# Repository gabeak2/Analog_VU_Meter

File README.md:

# Analog_VU_Meter

My First PCB - a VU-Meter with a microphone, and 2 LM3915 Bar Graph Displays.  It worked okay, there was always an issue with the crossover voltage of the LM3915s.  Reboots I did used MCUs, with much better results.

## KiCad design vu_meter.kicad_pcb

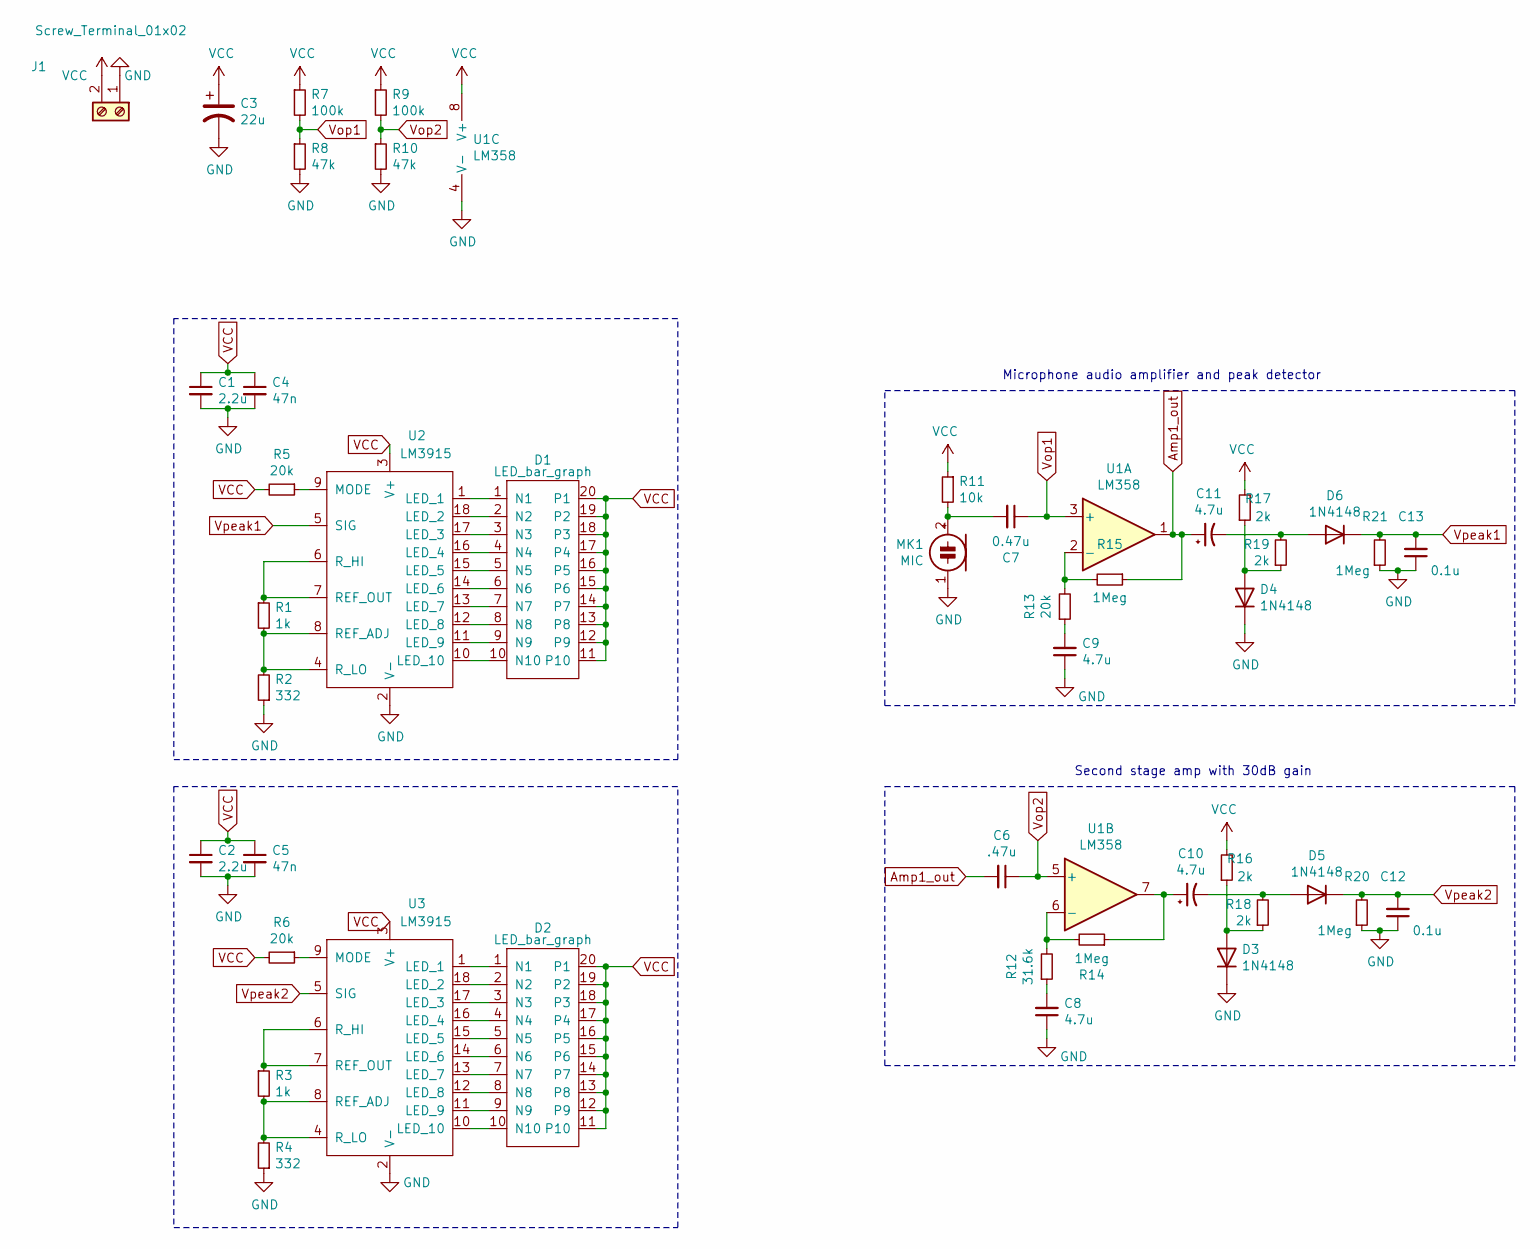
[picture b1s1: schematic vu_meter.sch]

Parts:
C1, C2: 2.2u; C_0805_2012Metric
C3: 22u; C_0805_2012Metric
C4, C5: 47n; C_0805_2012Metric
C6: .47u; C_0805_2012Metric
C7: 0.47u; C_0805_2012Metric
C8, C9, C10, C11: 4.7u; C_0805_2012Metric
C12, C13: 0.1u; C_0805_2012Metric
D1, D2: LED_bar_graph
D3, D4, D5, D6: 1N4148; D_DO-35_SOD27_P7.62mm_Horizontal
J1: Screw_Terminal_01x02; screw_terminal
MK1: MIC; screw_terminal
R1, R3: 1k; R_0805_2012Metric
R2, R4: 332; R_0805_2012Metric
R5, R6, R13: 20k; R_0805_2012Metric
R7, R9: 100k; R_0805_2012Metric
R8, R10: 47k; R_0805_2012Metric
R11: 10k; R_0805_2012Metric
R12: 31.6k; R_0805_2012Metric
R14, R15, R20, R21: 1Meg; R_0805_2012Metric
R16, R17, R18, R19: 2k; R_0805_2012Metric
U1: LM358; lm358
U2, U3: LM3915; LM3915_PDIP

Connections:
Amp1_out: C6.2, C11.1, R15.1, U1.1
GND: C1.2, C2.2, C3.2, C4.2, C5.2, C8.1, C9.1, C12.1, C13.1, D3.1 (K), D4.1 (K), J1.1, MK1.1 (-), R2.1, R4.1, R8.2, R10.2, R20.1, R21.1, U1.4 (V-), U2.2 (V-), U3.2 (V-)
unnamed: C7.2, MK1.2 (+), R11.2
unnamed: C8.2, R12.1
unnamed: C9.2, R13.1
unnamed: C10.1, R14.1, U1.7
unnamed: C10.2, D5.2 (A), R18.2
unnamed: C11.2, D6.2 (A), R19.2
unnamed: D1.1 (N1), U2.1 (LED_1)
unnamed: D1.2 (N2), U2.18 (LED_2)
unnamed: D1.3 (N3), U2.17 (LED_3)
unnamed: D1.4 (N4), U2.16 (LED_4)
unnamed: D1.5 (N5), U2.15 (LED_5)
unnamed: D1.6 (N6), U2.14 (LED_6)
unnamed: D1.7 (N7), U2.13 (LED_7)
unnamed: D1.8 (N8), U2.12 (LED_8)
unnamed: D1.9 (N9), U2.11 (LED_9)
unnamed: D1.10 (N10), U2.10 (LED_10)
unnamed: D2.1 (N1), U3.1 (LED_1)
unnamed: D2.2 (N2), U3.18 (LED_2)
unnamed: D2.3 (N3), U3.17 (LED_3)
unnamed: D2.4 (N4), U3.16 (LED_4)
unnamed: D2.5 (N5), U3.15 (LED_5)
unnamed: D2.6 (N6), U3.14 (LED_6)
unnamed: D2.7 (N7), U3.13 (LED_7)
unnamed: D2.8 (N8), U3.12 (LED_8)
unnamed: D2.9 (N9), U3.11 (LED_9)
unnamed: D2.10 (N10), U3.10 (LED_10)
unnamed: D3.2 (A), R16.1, R18.1
unnamed: D4.2 (A), R17.1, R19.1
unnamed: R1.1, U2.6 (R_HI), U2.7 (REF_OUT)
unnamed: R1.2, R2.2, U2.4 (R_LO), U2.8 (REF_ADJ)
unnamed: R3.1, U3.6 (R_HI), U3.7 (REF_OUT)
unnamed: R3.2, R4.2, U3.4 (R_LO), U3.8 (REF_ADJ)
unnamed: R5.1, U2.9 (MODE)
unnamed: R6.1, U3.9 (MODE)
unnamed: R12.2, R14.2, U1.6 (-)
unnamed: R13.2, R15.2, U1.2 (-)
VCC: C1.1, C2.1, C3.1, C4.1, C5.1, D1.11 (P10), D1.12 (P9), D1.13 (P8), D1.14 (P7), D1.15 (P6), D1.16 (P5), D1.17 (P4), D1.18 (P3), D1.19 (P2), D1.20 (P1), D2.11 (P10), D2.12 (P9), D2.13 (P8), D2.14 (P7), D2.15 (P6), D2.16 (P5), D2.17 (P4), D2.18 (P3), D2.19 (P2), D2.20 (P1), J1.2, R5.2, R6.2, R7.1, R9.1, R11.1, R16.2, R17.2, U1.8 (V+), U2.3 (V+), U3.3 (V+)
Vop1: C7.1, R7.2, R8.1, U1.3 (+)
Vop2: C6.1, R9.2, R10.1, U1.5 (+)
Vpeak1: C13.2, D6.1 (K), R21.2, U2.5 (SIG)
Vpeak2: C12.2, D5.1 (K), R20.2, U3.5 (SIG)

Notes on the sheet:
Microphone audio amplifier and peak detector
Second stage amp with 30dB gain

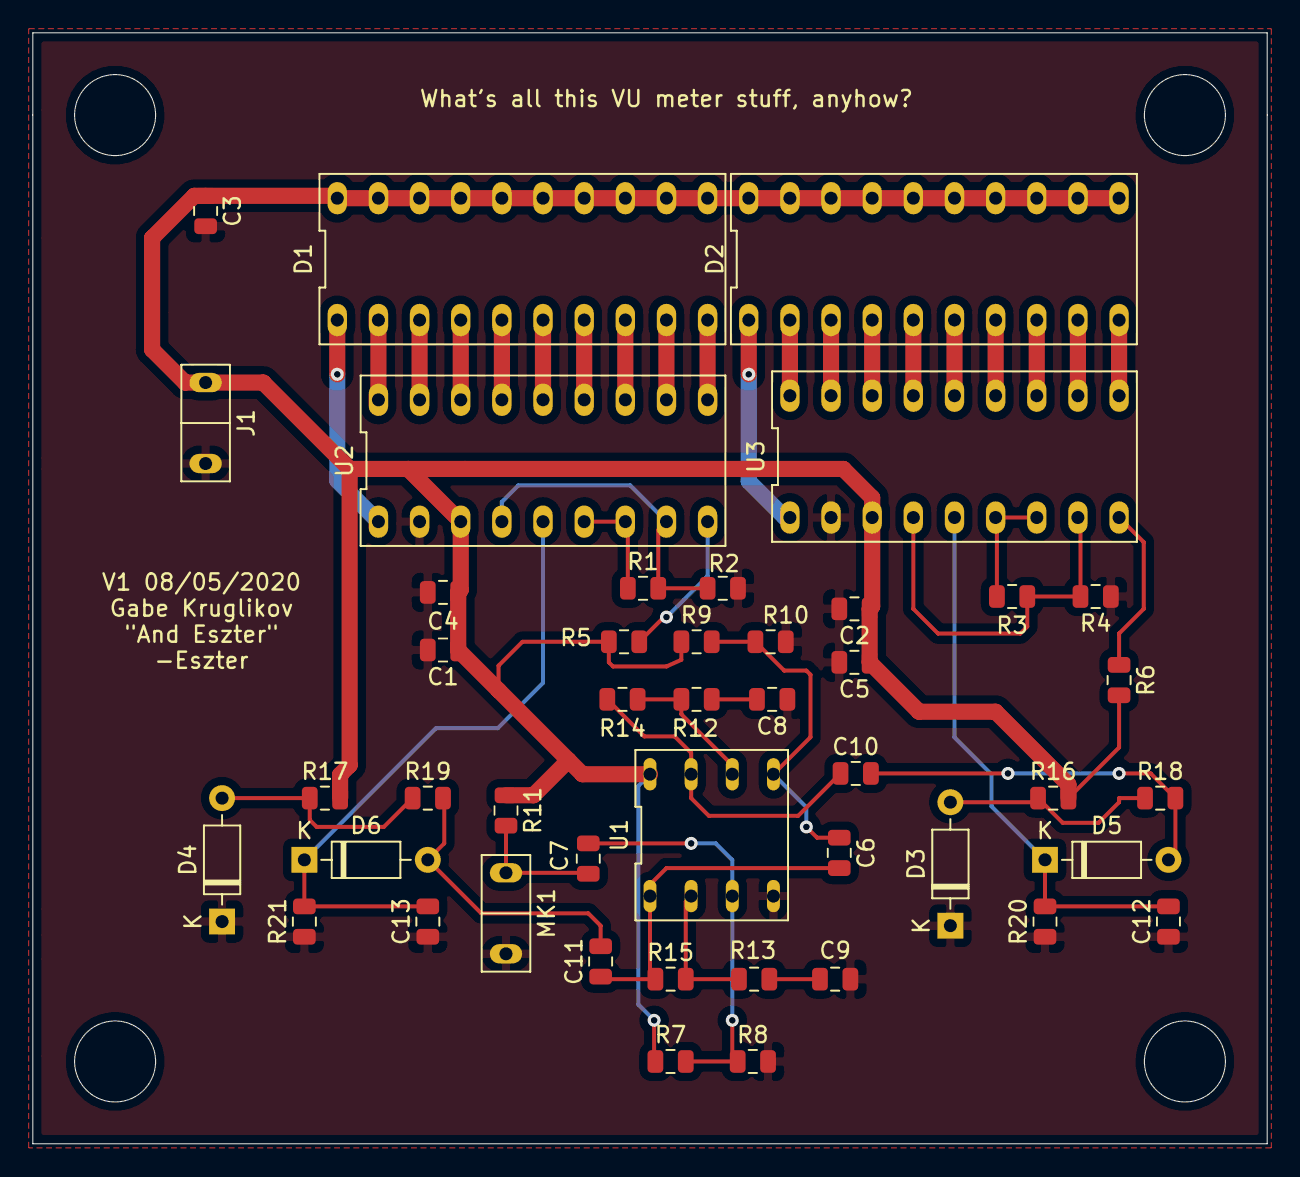
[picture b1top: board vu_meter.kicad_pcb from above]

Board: 2 copper layers, 76.2 x 68.6 mm, 45 parts (0 on the bottom side), 43 nets.

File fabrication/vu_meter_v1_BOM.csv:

"Id";"Designator";"Package";"Quantity";"Designation";"Supplier and ref";
1;"U3,U2";"LM3915_PDIP";2;"LM3915";;;
2;"U1";"lm358";1;"LM358";;;
3;"R21,R20,R15,R14";"R_0805_2012Metric";4;"1Meg";;;
4;"R19,R18,R17,R16";"R_0805_2012Metric";4;"2k";;;
5;"R13,R6,R5";"R_0805_2012Metric";3;"20k";;;
6;"R12";"R_0805_2012Metric";1;"31.6k";;;
7;"R11";"R_0805_2012Metric";1;"10k";;;
8;"R10,R8";"R_0805_2012Metric";2;"47k";;;
9;"R9,R7";"R_0805_2012Metric";2;"100k";;;
10;"R4,R2";"R_0805_2012Metric";2;"332";;;
11;"R3,R1";"R_0805_2012Metric";2;"1k";;;
12;"MK1";"screw_terminal";1;"MIC";;;
13;"J1";"screw_terminal";1;"Screw_Terminal_01x02";;;
14;"D6,D5,D4,D3";"D_DO-35_SOD27_P7.62mm_Horizontal";4;"1N4148";;;
15;"D2,D1";"LED_bar_graph";2;"LED_bar_graph";;;
16;"C13,C12";"C_0805_2012Metric";2;"0.1u";;;
17;"C11,C10,C9,C8";"C_0805_2012Metric";4;"4.7u";;;
18;"C7";"C_0805_2012Metric";1;"0.47u";;;
19;"C6";"C_0805_2012Metric";1;".47u";;;
20;"C5,C4";"C_0805_2012Metric";2;"47n";;;
21;"C3";"C_0805_2012Metric";1;"22u";;;
22;"C2,C1";"C_0805_2012Metric";2;"2.2u";;;
